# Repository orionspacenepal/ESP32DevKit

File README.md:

# ESP32DevKit
Development Board for ESP32

#### ESP32-WROOM-32 pinout

#### Pins availibility

#### Features
- [ ] Relay
- [X] OLED display
- [X] Push buttons
- [X] Temperature sensor DS18B20
- [X] SMD RGB LED
- [ ] LED on pin 2
- [ ] GPS module
- [ ] FTDI?

#### Changes, TODOs
- [ ] Add 3V3 with UART header
- [ ] Replace the pins: 6, 7, 9, 10, and 11
- [ ] Electrolytic capacitor to input volatage 
- [ ] Remove the use of buttons for flashing
- [ ] Add all communication protocols

#### Some notes
1. Using the pins that doesnot functions as GPIO output (like 6, 7, 9, 10, and 11) might result in disfunction of available pins too.

#### References
1. [Random Nerd Tutorials: ESP32 Pinout Reference: Which GPIO pins should you use?][random_nerd_pinout]
2. [Random Nerd Tutorials: Getting Started with the ESP32 Development Board][random_nerd_esp32]

[random_nerd_pinout]: https://randomnerdtutorials.com/esp32-pinout-reference-gpios/
[random_nerd_esp32]: https://randomnerdtutorials.com/getting-started-with-esp32/

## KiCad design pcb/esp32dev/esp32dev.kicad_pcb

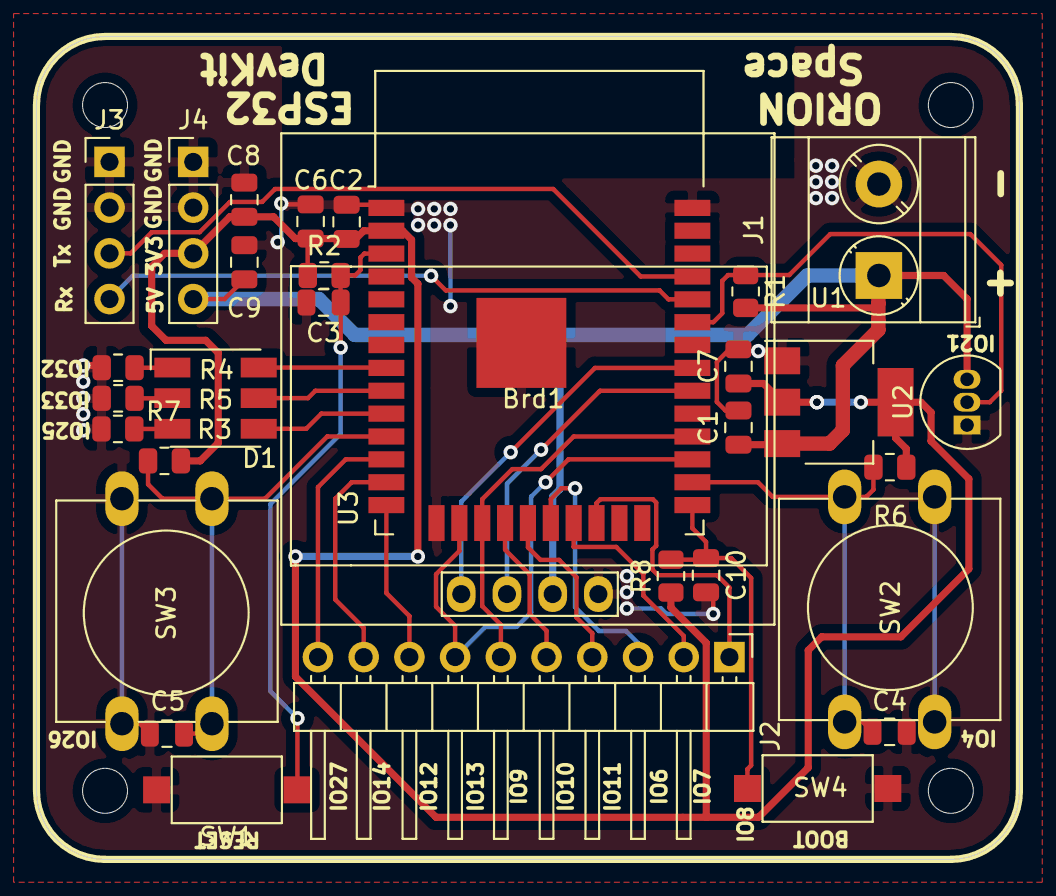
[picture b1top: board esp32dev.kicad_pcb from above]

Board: 2 copper layers, 54.6 x 45.7 mm, 31 parts (0 on the bottom side), 28 nets.

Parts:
Brd1: SSD1306; oled_ssd1306
C1, C2, C3, C4, C5, C6, C7, C8, C9, C10: C; C_0805_2012Metric
D1: LED_RGB; LED_RGB_5050-6
J1: power_input; TerminalBlock_Phoenix_MKDS-3-2-5.08_1x02_P5.08mm_Horizontal
J2: io_extenion; PinHeader_1x10_P2.54mm_Horizontal
J3, J4: power_extension; PinHeader_1x04_P2.54mm_Vertical
R1: 4.7k; R_0805_2012Metric
R2, R6, R7, R8: R; R_0805_2012Metric
R3, R4, R5: 220R; R_0805_2012Metric
SW1, SW4: SW_Push; SW_SPST_CK_RS282G05A3
SW2, SW3: SW_Push; SW_PUSH-12mm
U1: AMS1117-3.3; SOT-223-3_TabPin2
U2: DS18B20; TO-92_Inline
U3: ESP32-WROOM-32

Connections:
+3V3: C2.1, C6.1, C7.1, C8.1, J4.3, R2.1, R6.2, R7.2, R8.1, U1.2, U3.2
+5V: Brd1.2, C1.1, C9.1, J1.1, J4.4, R1.2, U1.3, U2.3
/boot: C10.1, R8.2, SW4.1, U3.25
/i012: J2.10, U3.12
/i013: J2.9, U3.13
/i014: J2.8, U3.14
/i016: J2.7, U3.16, U3.27
/i017: J2.6, U3.17, U3.28
/i018: J2.5, U3.18
/i019: J2.4, U3.19
/i020: J2.3, U3.20
/i021: J2.2, U3.21
/i022: J2.1, U3.22
/io8: D1.6, U3.8
/io9: D1.5, U3.9
/io10: D1.4, U3.10
/io11: C5.1, R7.1, SW3.1, U3.11
/io26: C4.1, R6.1, SW2.1, U3.26
/io33: R1.1, U2.2, U3.33
/reset: C3.1, R2.2, SW1.1, U3.3
/rx: J3.4, U3.34
/scl: Brd1.3, U3.30
/sda: Brd1.4, U3.31
/tx: J3.3, U3.35
GND: Brd1.1, C1.2, C2.2, C3.2, C4.2, C5.2, C6.2, C7.2, C8.2, C9.2, C10.2, J1.2, J3.1, J3.2, J4.1, J4.2, R3.1, R4.1, R5.1, SW1.2, SW2.2, SW3.2, SW4.2, U1.1, U2.1, U3.1, U3.15, U3.38, U3.39
unnamed: D1.1, R5.2
unnamed: D1.2, R4.2
unnamed: D1.3, R3.2

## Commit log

2022-04-11 Add PCB files
2022-05-06 Add docs
2022-05-06 Update references and TODOs
